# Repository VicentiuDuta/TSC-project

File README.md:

# OpenBook - E-book Reader

## Descriere generala

OpenBook este un dispozitiv de citit carti electronice (e-book reader) conceput pentru a fi ieftin si open-source.

## Diagrama bloc

## Bill Of Materials (BOM)
| Componenta                 | Link                                                                                                                                                                | Datasheet                                               |
|-----------------------------|-----------------------------------------------------------------------------------------------------------------------------------------------------------------------------|---------------------------------------------------------|
| BD5229G-TR                  | [Mouser](https://ro.mouser.com/ProductDetail/ROHM-Semiconductor/BD5229G-TR?qs=4kLU8WoGk0vvnhrrYwdszw%3D%3D)                                                                 | [Datasheet](https://fscdn.rohm.com/en/products/databook/datasheet/ic/power/voltage_detector/bd52xxg-e.pdf)|
| BME688                      | [Mouser](https://ro.mouser.com/ProductDetail/Bosch-Sensortec/BME688?qs=IS%252B4QmGtzzqQoVDscqwx3A%3D%3D)                                                           | [Datasheet](https://ro.mouser.com/datasheet/2/783/bst_bme688_fl000-2307034.pdf)|
| Bobina                      | [Mouser](https://ro.mouser.com/ProductDetail/Wurth-Elektronik/744043680?qs=PGXP4M47uW6VkZq%252BkzjrHA%3D%3D)                                                                | [Datasheet](https://www.we-online.com/components/products/datasheet/744043680.pdf)|
| Button                      | [Mouser](https://ro.mouser.com/ProductDetail/CK/KMR221GULCLFS?qs=u2NJ%252B70r0goBXaNk7IrU0Q%3D%3D)                                                                          |[Datasheet](https://www.ckswitches.com/media/1479/kmr2.pdf)|
| Capacitor 0.1uF / 50V       | [Farnell](https://ro.farnell.com/multicomp-pro/mcmlr50v104kx7r/ceramic-capacitor-0-1uf-50v-x7r/dp/1600875?srsltid=AfmBOop-NuqSwaWYAsNDvdMnjraBeqfj0sl8f99iLZ_KJc8xpnT4fSqT) | [Datasheet](https://www.farnell.com/datasheets/2873577.pdf?_gl=1*x28a2*_gcl_au*MTYwODAzNzc2OC4xNzQzNDM1MjM4)|
| Capacitor 1uF               | [Mouser](https://ro.mouser.com/ProductDetail/KEMET/C0402C105K9PACTU?qs=UdQET6xYxVCMExqTDkuPeQ%3D%3D)                                                                        | [Datasheet](https://ro.mouser.com/datasheet/2/447/KEM_C1006_X5R_SMD-3316465.pdf)|
| Capacitor 1uF / 50V         | [Mouser](https://ro.mouser.com/ProductDetail/TDK/C1608X7R1H105K080AB?qs=sGAEpiMZZMsh%252B1woXyUXjwVqLNpRsvnQGmKhuYn4DWE%3D)                                                 | [Datasheet](https://product.tdk.com/system/files/dam/doc/product/capacitor/ceramic/mlcc/catalog/mlcc_commercial_general_en.pdf)|
| Capacitor 4.7uF             | [Mouser](https://ro.mouser.com/ProductDetail/KEMET/C0402C475M9PAC7411?qs=cpo3%2FpBou2jRzZxyxJnMGg%3D%3D)                                                                    | [Datasheet](https://ro.mouser.com/datasheet/2/447/KEM_C1006_X5R_SMD-3316465.pdf)|
| Capacitor 4.7uF / 25V       | [Mouser](https://ro.mouser.com/ProductDetail/KYOCERA-AVX/12063C475KAZ2A?qs=%252BdQmOuGyFcG3LdbVp5waMw%3D%3D)                                                                | [Datasheet](https://ro.mouser.com/datasheet/2/40/X7RDielectric-2943470.pdf)|
| Capacitor 10uF              | [Mouser](https://ro.mouser.com/ProductDetail/KEMET/C0402C106M9PACTU?qs=x4XeXhDQKnp%252Bz0lMlwMC3A%3D%3D)                                                                    | [Datasheet](https://ro.mouser.com/datasheet/2/447/KEM_C1006_X5R_SMD-3316465.pdf)|
| Capacitor 100nF             | [Mouser](https://ro.mouser.com/ProductDetail/KEMET/C0402C104K4RAL?qs=pIZUS6sqCWCaMuP2QVR%2Fog%3D%3D)                                                                        | [Datasheet](https://ro.mouser.com/datasheet/2/447/KEM_C1018_X7R_SnPb_SMD-3316276.pdf)|
| Capacitor 100uF TANT        | [Mouser](https://ro.mouser.com/ProductDetail/KYOCERA-AVX/TAJW107M010RNJ?qs=Wtp%252Bf%2FAeVqIH8v1VxV%252B1Rg%3D%3D)                                                          | [Datasheet](https://ro.mouser.com/datasheet/2/40/TAJ-3165264.pdf)|
| Capacitor SUPERCAP          | [Mouser](https://ro.mouser.com/ProductDetail/Seiko-Semiconductors/CPH3225A?qs=3etwrb1wR%252BhUOph6lAO7eg%3D%3D)                                                             | [Datasheet](https://ro.mouser.com/datasheet/2/360/Seiko_Instruments_MicroBattery_E_20230330_2024Jan_-3561061.pdf)|
| CHG_LED                     | [CPC](https://cpc.farnell.com/kingbright/kpg-1608zgc/led-smd-0603-grn/dp/SC20796)                                                                                           | [Datasheet](https://www.farnell.com/datasheets/2046349.pdf)|
| DMG2305UX-7                 | [Mouser](https://ro.mouser.com/ProductDetail/Diodes-Incorporated/DMG2305UX-7?qs=L1DZKBg7t5F%2FNBHrjfxC%252Bg%3D%3D)                                                         | [Datasheet](https://www.diodes.com/assets/Datasheets/DMG2305UX.pdf)|
| DS3231SN#                   | [Mouser](https://ro.mouser.com/ProductDetail/Analog-Devices-Maxim-Integrated/DS3231SN?qs=1eQvB6Dk1vhUlr8%2FOrV0Fw%3D%3D)                                                    | [Datasheet](https://ro.mouser.com/datasheet/2/609/DS3231-3421123.pdf)|
| ESP32-C6-WROOM-1-N8         | [Mouser](https://ro.mouser.com/ProductDetail/Espressif-Systems/ESP32-C6-WROOM-1-N8?qs=8Wlm6%252BaMh8ST02Gmwp74cw%3D%3D)                                                    | [Datasheet](https://ro.mouser.com/datasheet/2/891/Espressif_ESP32_C6_WROOM_1__Datasheet_V0_1_PRELIMI-3239987.pdf)|
| FH34SRJ-24S-0.5SH_99_       | [Mouser](https://ro.mouser.com/ProductDetail/Hirose-Connector/FH34SRJ-24S-0.5SH99?qs=vcbW%252B4%252BSTIpKBl5ap9J8Fw%3D%3D)                                                  | [Datasheet](https://ro.mouser.com/datasheet/2/185/FH34SRJ_24S_0_5SH_99__CL0580_1255_6_99_2DDrawing_0-1615044.pdf)|
| 112A-TAAR-R03_ATTEND        | [LCSC](https://www.lcsc.com/product-detail/SD-Card-Connectors_Attend-Technology-112A-TAAR-R03_C6970445.html)                                                                | [Datasheet](https://www.lcsc.com/datasheet/lcsc_datasheet_2411220717_Attend-Technology-112A-TAAR-R03_C6970445.pdf)|
| MAX17048G+T10               | [Mouser](https://ro.mouser.com/ProductDetail/Analog-Devices-Maxim-Integrated/MAX17048G%2bT10?qs=D7PJwyCwLAoGnnn8jEPRBQ%3D%3D)                                               | [Datasheet](https://ro.mouser.com/datasheet/2/609/MAX17048_MAX17049-3469099.pdf)|
| MBR0530                     | [Mouser](https://ro.mouser.com/ProductDetail/onsemi/MBR0530T3G?qs=3JMERSakebpEmdUS6GetdQ%3D%3D)                                                                             | [Datasheet](https://www.onsemi.com/products/discrete-power-modules/schottky-diodes-schottky-rectifiers/mbr0530t3g)|
| MCP73831                    | [Mouser](https://ro.mouser.com/ProductDetail/Microchip-Technology/MCP73831-2ACI-MC?qs=hH%252BOa0VZEiBneYTVdpuVdg%3D%3D)                                                     | [Datasheet](https://ro.mouser.com/datasheet/2/268/MCP73831_Family_Data_Sheet_DS20001984H-3441711.pdf)|
| PFMF.050.1                  | [Mouser](https://ro.mouser.com/ProductDetail/Schurter/PFMF.050.2?qs=1auRipcfynCums5v1iucSA%3D%3D)                                                                           | [Datasheet](https://ro.mouser.com/datasheet/2/358/typ_PFMF-1275918.pdf)|
| PGB1010603MR                | [Mouser](https://ro.mouser.com/ProductDetail/Littelfuse/PGB1010603MR?qs=gu7KAQ731URLg4GSnNNN7Q%3D%3D)                                                                       | [Datasheet](https://www.littelfuse.com/assetdocs/pulseguard-esd-suppressors-pgb1-datasheet?assetguid=8a337998-d54d-466b-be4e-dc5bcd1f9321)|
| QWIIC_RIGHT_ANGLEA          | [Mouser](https://ro.mouser.com/ProductDetail/JST-Commercial/SM04B-SRSS-TBLFSN?qs=cdbOS8ANM9B3FdyA6cNU2A%3D%3D)                                                              | [Datasheet](https://ro.mouser.com/datasheet/2/564/eSR_SZ-3476820.pdf)|
| Resistor 0.47               | [Mouser](https://ro.mouser.com/ProductDetail/Vishay-Beyschlag/MCT06030C4700FP500?qs=XsZ9OvPb0dt82KlzjdcMjQ%3D%3D)                                                           | [Datasheet](https://www.vishay.com/docs/28705/mcx0x0xpro.pdf)|
| Resistor 2k                 | [Venkel](https://www.venkel.com/part/CR0402-16W-2002FT)                                                                                                                     | [Datasheet](https://data.venkel.com/documents/cr-series?_gl=1*1sqolfs*_ga*MTAzMTIxOTYyMS4xNzQzNzU5MjAy*_ga_JRKGBZNVM8*MTc0Mzc1OTIwMS4xLjEuMTc0Mzc1OTY2OS4zNC4wLjA.)|
| Resistor 5k1                | [Venkel](https://venkel.com/part/CR0402-10W-5101FT)                                                                                                                         | [Datasheet](https://data.venkel.com/documents/cr-series?_gl=1*1e041jc*_ga*MTAzMTIxOTYyMS4xNzQzNzU5MjAy*_ga_JRKGBZNVM8*MTc0Mzc1OTIwMS4xLjEuMTc0Mzc1OTU2Ny41MS4wLjA.)|
| Resistor 10K                | [DigiKey](https://www.digikey.com/en/products/detail/venkel/CR0402-10W-102JT/12332774)                                                                                      | [Datasheet](https://data.venkel.com/documents/cr-series?_gl=1*mn27ew*_ga*MTAzMTIxOTYyMS4xNzQzNzU5MjAy*_ga_JRKGBZNVM8*MTc0Mzc1OTIwMS4xLjAuMTc0Mzc1OTIwMi41OS4wLjA.)|
| Resistor 100K               | [Venkel](https://venkel.com/part/CR0402-16W-1003FT)                                                                                                                         | [Datasheet](https://data.venkel.com/documents/cr-series?_gl=1*oleae1*_ga*MTAzMTIxOTYyMS4xNzQzNzU5MjAy*_ga_JRKGBZNVM8*MTc0Mzc1OTIwMS4xLjEuMTc0Mzc1OTM0My4zNi4wLjA.)|
| SAMACSYS_PARTS_USB4110-GF-A | [Mouser](https://ro.mouser.com/ProductDetail/GCT/USB4110-GF-A?qs=KUoIvG%2F9IlYiZvIXQjyJeA%3D%3D)                                                            | [Datasheet](https://ro.mouser.com/datasheet/2/837/GCT_USB4110_Product_Drawing___20k_cycles-3455479.pdf)|
| SD0805S020S1R0              | [Mouser](https://ro.mouser.com/ProductDetail/KYOCERA-AVX/SD0805S020S1R0?qs=jCA%252BPfw4LHbpkAoSnwrdjw%3D%3D)                                                                | [Datasheet](https://ro.mouser.com/datasheet/2/40/schottky-3165252.pdf)|
| SI1308EDL-T1-GE3            | [Mouser](https://ro.mouser.com/ProductDetail/Vishay-Semiconductors/SI1308EDL-T1-GE3?qs=bX1%252BNvsK%2FBramh9tgpOaEw%3D%3D)                                                  | [Datasheet](https://www.vishay.com/docs/63399/si1308edl.pdf)|
| USBLC6-2SC6Y                | [Mouser](https://ro.mouser.com/ProductDetail/STMicroelectronics/USBLC6-2SC6Y?qs=gNDSiZmRJS%2FOgDexvXkdow%3D%3D)                                                             | [Datasheet](https://ro.mouser.com/datasheet/2/389/usblc6_2sc6y-1852505.pdf)|
| W25Q512JVEIQ                | [Mouser](https://ro.mouser.com/ProductDetail/Winbond/W25Q512JVEIQ?qs=l7cgNqFNU1jw6svr3at6tA%3D%3D)                                                           | [Datasheet](https://ro.mouser.com/datasheet/2/949/Winbond_W25Q512JV_Datasheet-3240039.pdf)|
| XC6220A331MR-G              | [Mouser](https://ro.mouser.com/ProductDetail/Torex-Semiconductor/XC6220A331MR-G?qs=AsjdqWjXhJ8ZSWznL1J0gg%3D%3D)                                                            | [Datasheet](https://ro.mouser.com/datasheet/2/760/xc6220-3371556.pdf)|

## Descrierea functionalitatii hardware

### Sistem de alimentare si gestionare a energiei

Dispozitivul OpenBook implementeaza un sistem dual de alimentare, functionand atat prin conectorul USB-C cat si prin bateria reincarcabila Li-Po. Modulul MCP73831 gestioneaza procesul de incarcare inteligenta a bateriei, asigurand protectie la supraincarcare si optimizarea ciclurilor de incarcare. Convertorul LDO XC6220A331MR-G stabilizeaza tensiunea la 3.3V pentru toate componentele electronice, asigurand functionarea eficienta a sistemului.

Pentru alimentarea afisajului e-paper, care necesita tensiuni specifice, am proiectat un circuit dedicat bazat pe bobina inductiva 744043680 si diode Schottky pentru generarea si stabilizarea tensiunilor necesare functionarii optime a ecranului.

### Unitatea centrala de procesare

La baza sistemului se afla modulul ESP32-C6-WROOM-1-N8, care integreaza microcontrolerul ESP32-C6 impreuna cu conectivitate wireless WiFi si Bluetooth. Acesta coordoneaza toate operatiunile dispozitivului, de la gestionarea interfetei cu utilizatorul pana la procesarea si afisarea textului. Designul include butoane dedicate pentru reset si boot, facilitand atat utilizarea normala cat si procesele de dezvoltare si depanare.

### Sisteme de conectivitate si interfete

- **Portul USB-C**: Asigura atat alimentarea si incarcarea bateriei cat si transferul de date pentru gestionarea bibliotecii digitale
- **Slotul microSD**: Permite extinderea capacitatii de stocare pentru biblioteci extinse de carti electronice
- **Conectorul FPC cu 24 pini**: Interfata specializata pentru afisajul e-paper de 7.5 inch
- **Conectorul Qwiic/Stemma QT**: Faciliteaza integrarea modulara a senzorilor si perifericelor I2C aditionale

### Subsisteme de stocare si functii auxiliare

- **Memoria flash W25Q512JVEIQ**: Ofera 64MB de spatiu de stocare persistent pentru sistemul de operare si datele utilizatorului
- **Modulul RTC DS3231**: Mentine cronometrarea precisa a timpului real, chiar si cand dispozitivul este oprit, datorita sistemului de backup cu supercapacitor
- **Senzorul ambiental BME688**: Monitorizeaza conditiile de mediu (temperatura, umiditate, presiune atmosferica si calitatea aerului) pentru ajustarea optima a parametrilor de afisare
- **Circuitul integrat MAX17048**: Monitorizeaza cu precizie starea bateriei si ofera utilizatorului informatii despre autonomia ramasa

## Design Log
- Am modificat pozitionarea butoanelor din carcasa pentru a se potrivi cu cele de pe PCB.
- Am aprobat 2 erori DRC de dimenisiune pentru USB, conform enuntului.

## Descrierea pinilor ESP32-C6 utilizati

| Pin ESP32-C6 | Functie | Descriere |
|--------------|---------|-----------|
| IO0 | INT_RTC | Semnal de intrerupere de la RTC |
| IO1 | 32KHZ | Semnal de ceas de la RTC |
| IO2 | MISO | Comunicatie SPI cu cardul SD|
| IO3 | EPD_BUSY | Semnal ocupat de la e-paper |
| IO4, IO5 | SS_SD, EPD_DC | Selectie card SD si control date/comanda e-paper |
| IO6, IO7 | SCK, MOSI | Clock SPI si date de iesire |
| IO8 | GPIO8 | Pin de uz general |
| IO9 | IO/BOOT | Buton de boot |
| IO10, IO11 | EPD_CS, FLASH_CS | Selectie chip pentru display si memoria flash |
| IO12, IO13 | USB_D-, USB_D+ | Comunicatii USB |
| IO15 | IO/CHANGE | Buton de schimbare pagina |
| IO16 | TX | Transmitere seriala (UART) |
| IO17 | RX | Receptie seriala (UART) |
| IO18 | RTC_RST | Reset pentru RTC |
| IO19 | I2C_PW | Control alimentare pentru perifericele I2C |
| IO20 | EPD_3V3_C | Control alimentare pentru display |
| IO21, IO22 | SDA, SCL | Comunicatii I2C |
| IO23 | EPD_RST | Reset pentru display |
| EN | RESET | Semnal de reset pentru ESP32 |

## Imagini:

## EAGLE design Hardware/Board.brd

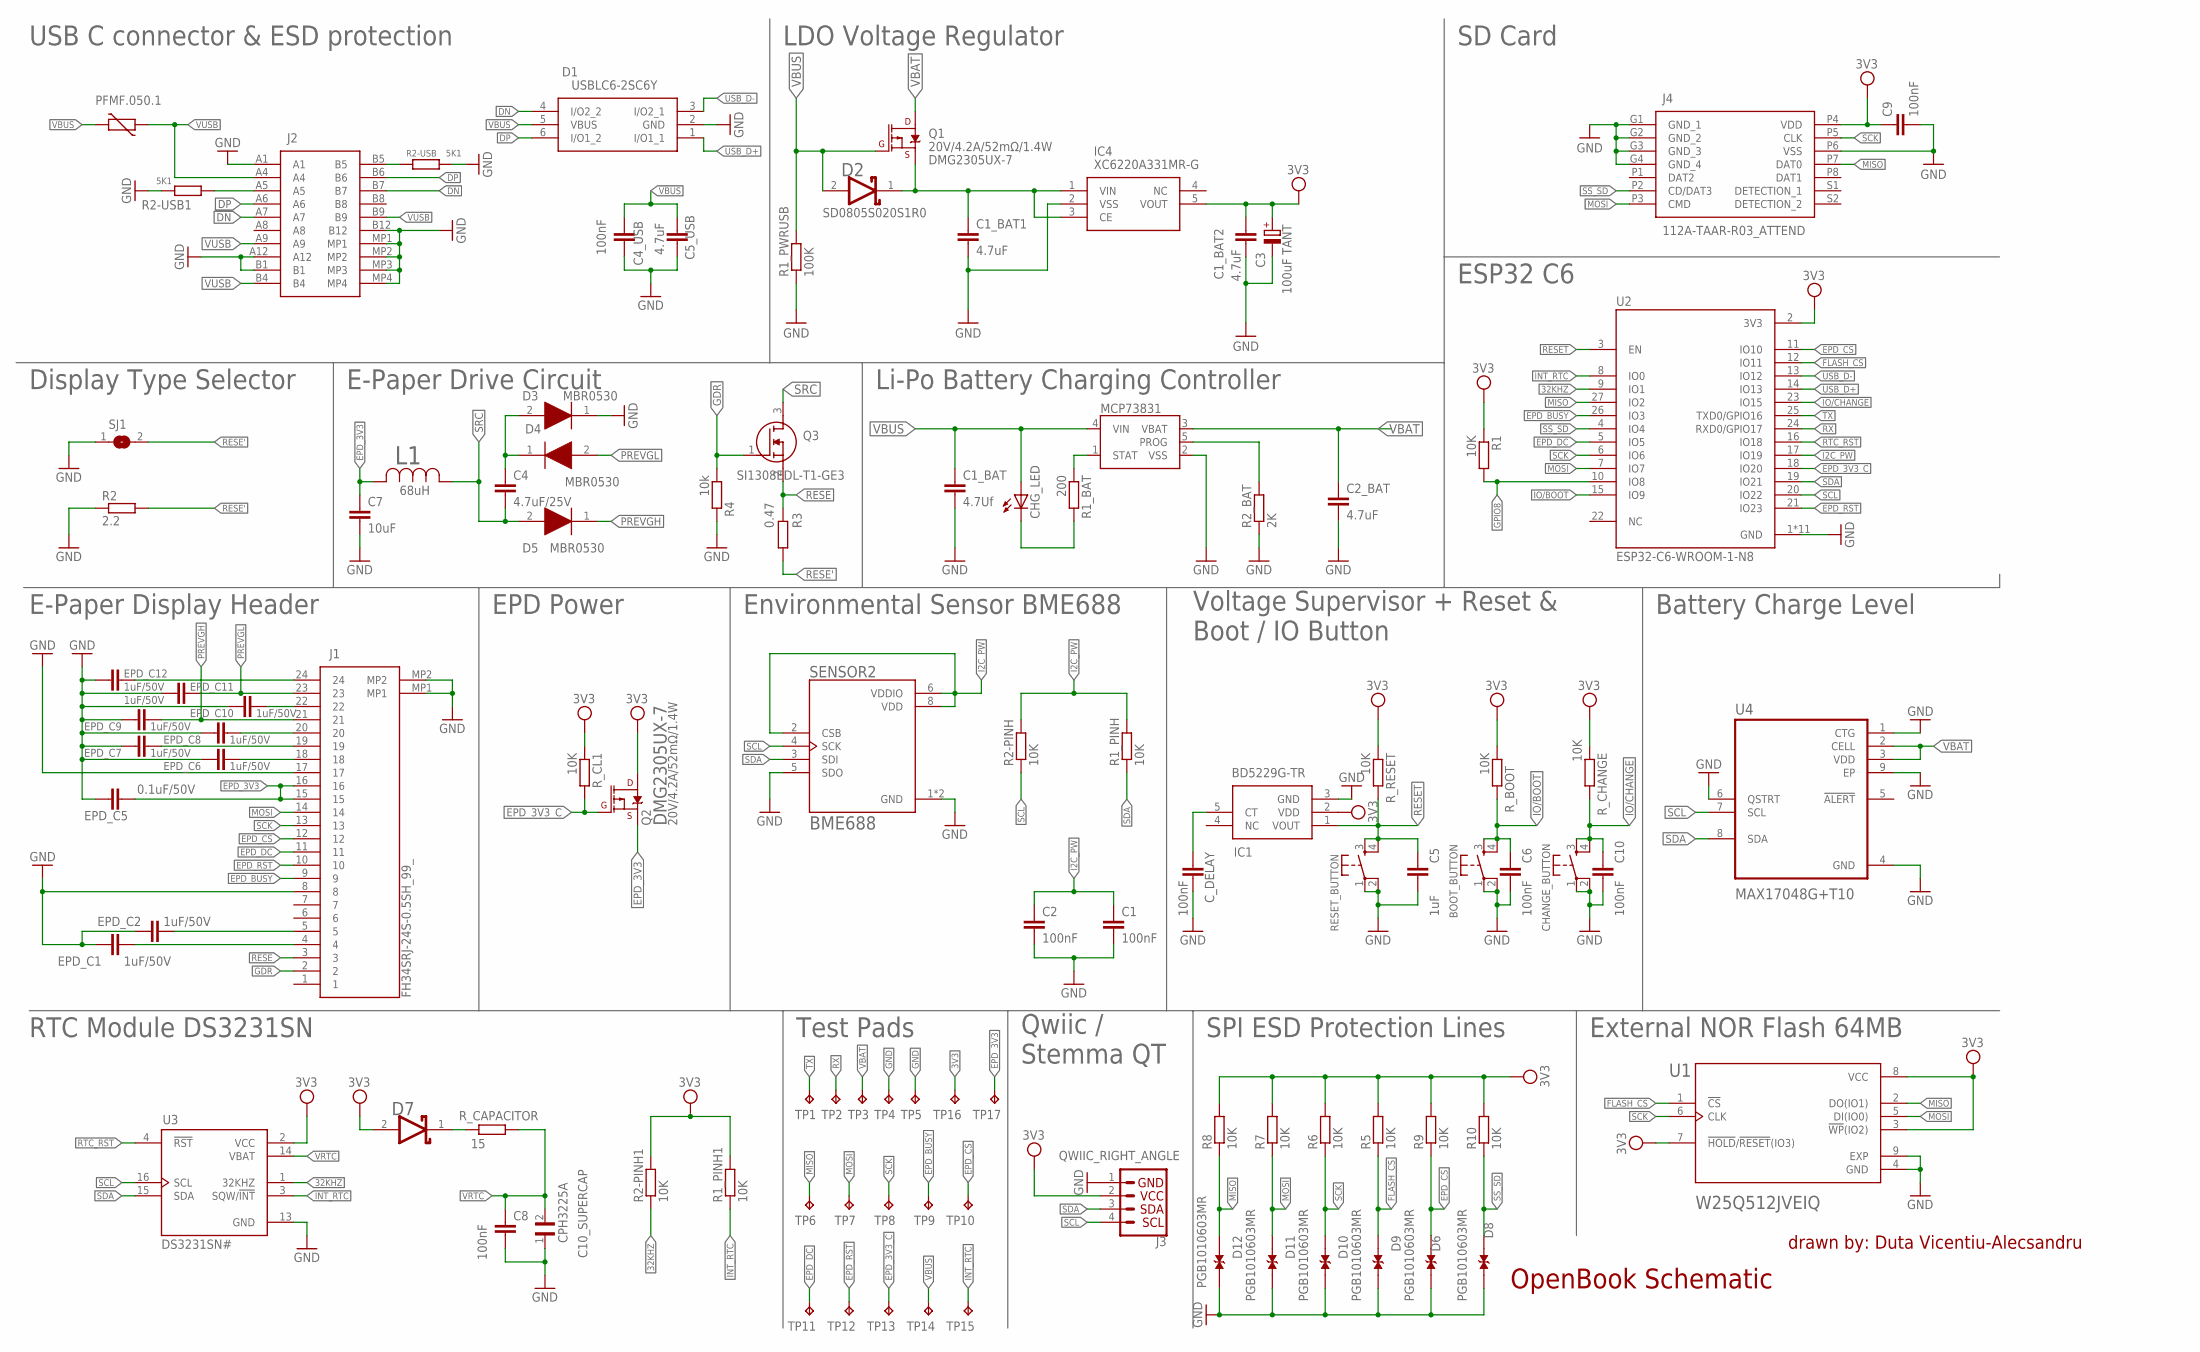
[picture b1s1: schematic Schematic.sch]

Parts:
BOOT_BUTTON: BUTTON_CUSYOMV1; MYBUTTON
C1, C2, C4_USB, C6, C8, C9, C10: 100nF; EAGLE-LTSPICE_C0402
C1_BAT: 4.7Uf; EAGLE-LTSPICE_C0402
C1_BAT1, C1_BAT2, C2_BAT, C5_USB: 4.7uF; EAGLE-LTSPICE_C0402
C3: 100uF TANT; RCL_CT3528
C4: 4.7uF/25V; EAGLE-LTSPICE_C0402
C5: 1uF; EAGLE-LTSPICE_C0402
C7: 10uF; EAGLE-LTSPICE_C0402
C10_SUPERCAP: CPH3225A; CAPCP3225X100N
CHANGE_BUTTON: BUTTON_CUSYOMV1; MYBUTTON
CHG_LED: ADAFRUIT_LEDCHIP-LED0603; ADAFRUIT_CHIP-LED0603
C_DELAY: 100nF; EAGLE-LTSPICE_C0402
D1: USBLC6-2SC6Y; SOT95P280X145-6N
D2, D7: ESP32_WROVER_AVX---SD0805S020S1R0_AVX_SD0805S020S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; ESP32_WROVER_AVX---SD0805S020S1R0_AVX_SD0805S020S1R0_0
D3, D4, D5: MBR0530; SOD3716X135N
D6, D8, D9, D10, D11, D12: PGB1010603MR; DIOC1608X36N
EPD_C1, EPD_C2, EPD_C6, EPD_C7, EPD_C8, EPD_C9, EPD_C10, EPD_C11, EPD_C12: 1uF/50V; EAGLE-LTSPICE_C0402
EPD_C5: 0.1uF/50V; EAGLE-LTSPICE_C0402
IC1: BD5229G-TR; SOT95P280X125-5N
IC4: XC6220A331MR-G; SOT95P280X120-5N
J1: FH34SRJ-24S-0.5SH_99_; FH34SRJ24S05SH99
J2: SAMACSYS_PARTS_USB4110-GF-A; SAMACSYS_PARTS_USB4110GFA
J3: QWIIC_RIGHT_ANGLE; JST04_1MM_RA
J4: 112A-TAAR-R03_ATTEND; 112ATAARR03ATTEND
L1: 744043680IND_4828-WE-TPC_WRE; IND_4828-WE-TPC_WRE
MCP73831: ESP32_WROVER_SPARKFUN-IC-POWER_MCP73831; ESP32_WROVER_SPARKFUN-IC-POWER_SOT23-5
PFMF.050.1: ESP32C6_VARISTORCN1812; ESP32C6_VARISTOR_CT/CN1812
Q1, Q2: 20V/4.2A/52mΩ/1.4W; ESP32_WROVER_SPARKFUN-DISCRETESEMI_SOT23-3
Q3: SI1308EDL-T1-GE3; SOT65P210X110-3N
R1, R1_PINH, R1_PINH1, R2-PINH, R2-PINH1, R5, R6, R7, R8, R9, R10: 10K; ESP32_WROVER_EAGLE-LTSPICE_R0402
R1_BAT: 200; ESP32_WROVER_EAGLE-LTSPICE_R0402
R1_PWRUSB: 100K; ESP32_WROVER_EAGLE-LTSPICE_R0402
R2: 2.2; ESP32_WROVER_EAGLE-LTSPICE_R0402
R2-USB, R2-USB1: 5K1; ESP32_WROVER_EAGLE-LTSPICE_R0402
R2_BAT: 2K; ESP32_WROVER_EAGLE-LTSPICE_R0402
R3: 0.47; ESP32_WROVER_EAGLE-LTSPICE_R0402
R4: 10k; ESP32_WROVER_EAGLE-LTSPICE_R0402
RESET_BUTTON: BUTTON_CUSYOMV1; MYBUTTON
R_BOOT: 10K; ESP32_WROVER_EAGLE-LTSPICE_R0402
R_CAPACITOR: 15; ESP32_WROVER_EAGLE-LTSPICE_R0402
R_CHANGE: 10K; ESP32_WROVER_EAGLE-LTSPICE_R0402
R_CL1: 10K; ESP32_WROVER_EAGLE-LTSPICE_R0402
R_RESET: 10K; ESP32_WROVER_EAGLE-LTSPICE_R0402
SENSOR2: ESP32_WROVER_BME680_BME680; ESP32_WROVER_BME680_PSON80P300X300X100-8N
SJ1: SJ
TP1, TP2, TP3, TP4, TP5, TP6, TP7, TP8, TP9, TP10, TP11, TP12, TP13, TP14, TP15, TP16, TP17: TPTP20R; TP20R
U1: W25Q512JVEIQ; SON127P600X800X80-9N
U2: ESP32-C6-WROOM-1-N8; XCVR_ESP32-C6-WROOM-1-N8
U3: DS3231SN#; SOIC127P1032X265-16N
U4: MAX17048G+T10; SON50P200X200X80-9N

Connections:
3V3: C1_BAT2.1, C3.+, C9.1, D7.2 (ANODE), IC1.2 (VDD), IC4.5 (VOUT), J3.2, J4.P4 (VDD), Q2.3 (D), R1.1, R1_PINH1.2, R2-PINH1.2, R5.2, R6.2, R7.2, R8.2, R9.2, R10.2, R_BOOT.1, R_CHANGE.1, R_CL1.1, R_RESET.1, TP16.TP, U1.3 (!WP!(IO2)), U1.7 (!HOLD!/!RESET!(IO3)), U1.8 (VCC), U2.2 (3V3), U3.2 (VCC)
32KHZ: R2-PINH1.1, U2.9 (IO1), U3.1 (32KHZ)
DN: D1.4 (I/O2_2), J2.A7, J2.B7
DP: D1.6 (I/O1_2), J2.A6, J2.B6
EPD_3V3: C7.1, EPD_C5.1, J1.15, J1.16, L1.2, Q2.2 (S), TP17.TP
EPD_3V3_C: Q2.1 (G), R_CL1.2, TP13.TP, U2.18 (IO20)
EPD_BUSY: J1.9, TP9.TP, U2.26 (IO3)
EPD_CS: D6.1, J1.12, R9.1, TP10.TP, U2.11 (IO10)
EPD_DC: J1.11, TP11.TP, U2.5 (IO5)
EPD_RST: J1.10, TP12.TP, U2.21 (IO23)
FLASH_CS: D9.1, R5.1, U1.1 (!CS), U2.12 (IO11)
GDR: J1.2, Q3.1 (G), R4.1
GND: BOOT_BUTTON.1, BOOT_BUTTON.2, C1.2, C1_BAT.2, C1_BAT1.2, C1_BAT2.2, C2.2, C2_BAT.2, C3.-, C4_USB.2, C5.2, C5_USB.2, C6.2, C7.2, C8.2, C9.2, C10.2, C10_SUPERCAP.1, CHANGE_BUTTON.1, CHANGE_BUTTON.2, C_DELAY.2, D1.2 (GND), D3.1 (K), D6.2, D8.2, D9.2, D10.2, D11.2, D12.2, EPD_C1.2, EPD_C2.2, EPD_C5.2, EPD_C6.2, EPD_C7.2, EPD_C8.2, EPD_C9.2, EPD_C10.2, EPD_C11.2, EPD_C12.2, IC1.3 (GND), IC4.2 (VSS), J1.8, J1.17, J1.MP1, J1.MP2, J2.A1, J2.A12, J2.B1, J2.B12, J2.MP1, J2.MP2, J2.MP3, J2.MP4, J3.1, J4.G1 (GND_1), J4.G2 (GND_2), J4.G3 (GND_3), J4.G4 (GND_4), J4.P6 (VSS), MCP73831.2 (VSS), R1_PWRUSB.1, R2.1, R2-USB.2, R2-USB1.1, R2_BAT.1, R4.2, RESET_BUTTON.1, RESET_BUTTON.2, SENSOR2.1 (GND), SENSOR2.5 (SDO), SENSOR2.7 (GND), SJ1.1, TP4.TP, TP5.TP, U1.4 (GND), U1.9 (EXP), U2.1 (GND), U2.28 (GND), U2.29_1 (GND), U2.29_2 (GND), U2.29_3 (GND), U2.29_4 (GND), U2.29_5 (GND), U2.29_6 (GND), U2.29_7 (GND), U2.29_8 (GND), U2.29_9 (GND), U3.13 (GND), U4.1 (CTG), U4.4 (GND), U4.6 (QSTRT), U4.9 (EP)
GPIO8: R1.2, U2.10 (IO8)
I2C_PW: C1.1, C2.1, R1_PINH.2, R2-PINH.2, SENSOR2.2 (CSB), SENSOR2.6 (VDDIO), SENSOR2.8 (VDD), U2.17 (IO19)
INT_RTC: R1_PINH1.1, TP15.TP, U2.8 (IO0), U3.3 (SQW/!INT)
IO/BOOT: BOOT_BUTTON.3, BOOT_BUTTON.4, C6.1, R_BOOT.2, U2.15 (IO9)
IO/CHANGE: C10.1, CHANGE_BUTTON.3, CHANGE_BUTTON.4, R_CHANGE.2, U2.23 (IO15)
MISO: D12.1, J4.P7 (DAT0), R8.1, TP6.TP, U1.2 (DO(IO1)), U2.27 (IO2)
MOSI: D11.1, J1.14, J4.P3 (CMD), R7.1, TP7.TP, U1.5 (DI(IO0)), U2.7 (IO7)
unnamed: J2.B5, R2-USB.1
unnamed: MCP73831.1 (STAT), R1_BAT.1
unnamed: C1_BAT1.1, D2.1 (CATHODE), IC4.1 (VIN), IC4.3 (CE), Q1.2 (S)
unnamed: MCP73831.5 (PROG), R2_BAT.2
unnamed: C4.1, D3.2 (A), D4.1 (K)
unnamed: CHG_LED.C, R1_BAT.2
unnamed: C_DELAY.1, IC1.5 (CT)
unnamed: EPD_C2.1, J1.5
unnamed: EPD_C1.1, J1.4
unnamed: EPD_C6.1, J1.18
unnamed: J2.A5, R2-USB1.2
unnamed: EPD_C8.1, J1.20
unnamed: EPD_C7.1, J1.19
unnamed: EPD_C10.1, J1.22
unnamed: EPD_C12.1, J1.24
unnamed: D7.1 (CATHODE), R_CAPACITOR.2
PREVGH: D5.1 (K), EPD_C9.1, J1.21
PREVGL: D4.2 (A), EPD_C11.1, J1.23
RESE: J1.3, Q3.2 (S), R3.2
RESE': R2.2, R3.1, SJ1.2
RESET: C5.1, IC1.1 (VOUT), RESET_BUTTON.3, RESET_BUTTON.4, R_RESET.2, U2.3 (EN)
RTC_RST: U2.16 (IO18), U3.4 (!RST)
RX: TP2.TP, U2.24 (RXD0/GPIO17)
SCK: D10.1, J1.13, J4.P5 (CLK), R6.1, TP8.TP, U1.6 (CLK), U2.6 (IO6)
SCL: J3.4, R2-PINH.1, SENSOR2.4 (SCK), U2.20 (IO22), U3.16 (SCL), U4.7 (SCL)
SDA: J3.3, R1_PINH.1, SENSOR2.3 (SDI), U2.19 (IO21), U3.15 (SDA), U4.8 (SDA)
SRC: C4.2, D5.2 (A), L1.1, Q3.3 (D)
SS_SD: D8.1, J4.P2 (CD/DAT3), R10.1, U2.4 (IO4)
TX: TP1.TP, U2.25 (TXD0/GPIO16)
USB_D+: D1.1 (I/O1_1), U2.14 (IO13)
USB_D-: D1.3 (I/O2_1), U2.13 (IO12)
VBAT: C2_BAT.1, MCP73831.3 (VBAT), Q1.3 (D), TP3.TP, U4.2 (CELL), U4.3 (VDD)
VBUS: C1_BAT.1, C4_USB.1, C5_USB.1, CHG_LED.A, D1.5 (VBUS), D2.2 (ANODE), MCP73831.4 (VIN), PFMF.050.1.2, Q1.1 (G), R1_PWRUSB.2, TP14.TP
VRTC: C8.1, C10_SUPERCAP.2, R_CAPACITOR.1, U3.14 (VBAT)
VUSB: J2.A4, J2.A9, J2.B4, J2.B9, PFMF.050.1.1

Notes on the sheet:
USB C connector & ESD protection
LDO Voltage Regulator
DMG2305UX-7
SD0805S020S1R0
SD Card
ESP32 C6
Li-Po Battery Charging Controller
E-Paper Drive Circuit
68uH
Display Type Selector
Battery Charge Level
Voltage Supervisor + Reset & Boot / IO Button
CHANGE_BUTTON
BOOT_BUTTON
RESET_BUTTON
Environmental Sensor BME688
BME688
EPD Power
E-Paper Display Header
RTC Module DS3231SN
Test Pads
Qwiic / Stemma QT
OpenBook Schematic
SPI ESD Protection Lines
External NOR Flash 64MB
drawn by: Duta Vicentiu-Alecsandru

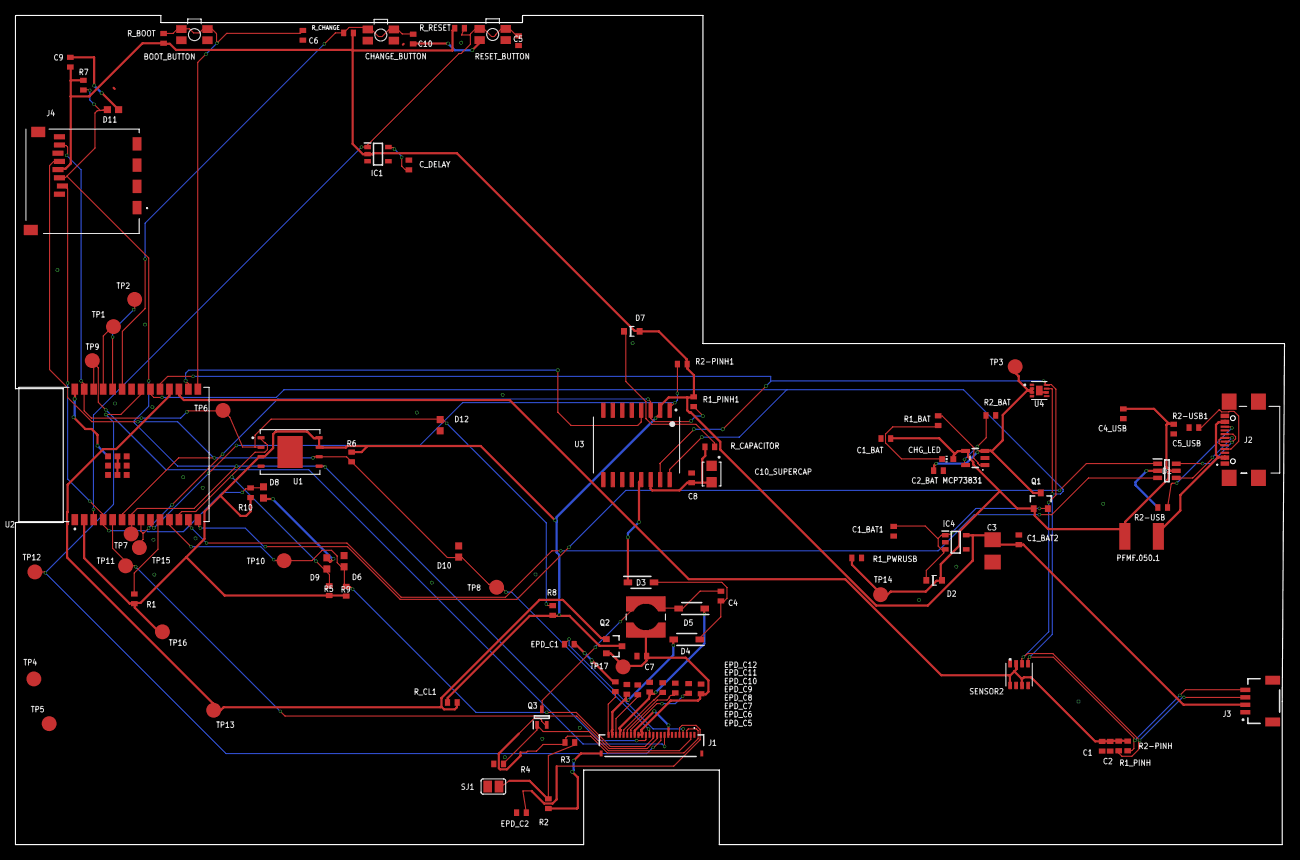
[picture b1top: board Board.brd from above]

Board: 2 copper layers, 170.2 x 111.2 mm, 103 parts (0 on the bottom side), 55 nets.

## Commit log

2025-04-05 first readme
2025-04-05 corrected readme
2025-04-05 Create LICENSE
2025-04-05 Update LICENSE
2025-04-06 Added images to readme
2025-04-10 Remaining exploded view and manufacturing
2025-04-14 FInal version of files. Remaining gerbers
2025-04-14 added gerbers.zip

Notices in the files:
parts and their libraries:
COPYRIGHT: Copyright (C) 2024 Ultra Librarian. All rights reserved.
